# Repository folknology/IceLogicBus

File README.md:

# IceLogicBus
#### IceLogicBus is an Ice40 Hx based MidPlane for robust [Tile](https://github.com/folknology/Tiles) expansion

#### IceLogicBus PCB

#### PCB Top

#### PCB Bottom

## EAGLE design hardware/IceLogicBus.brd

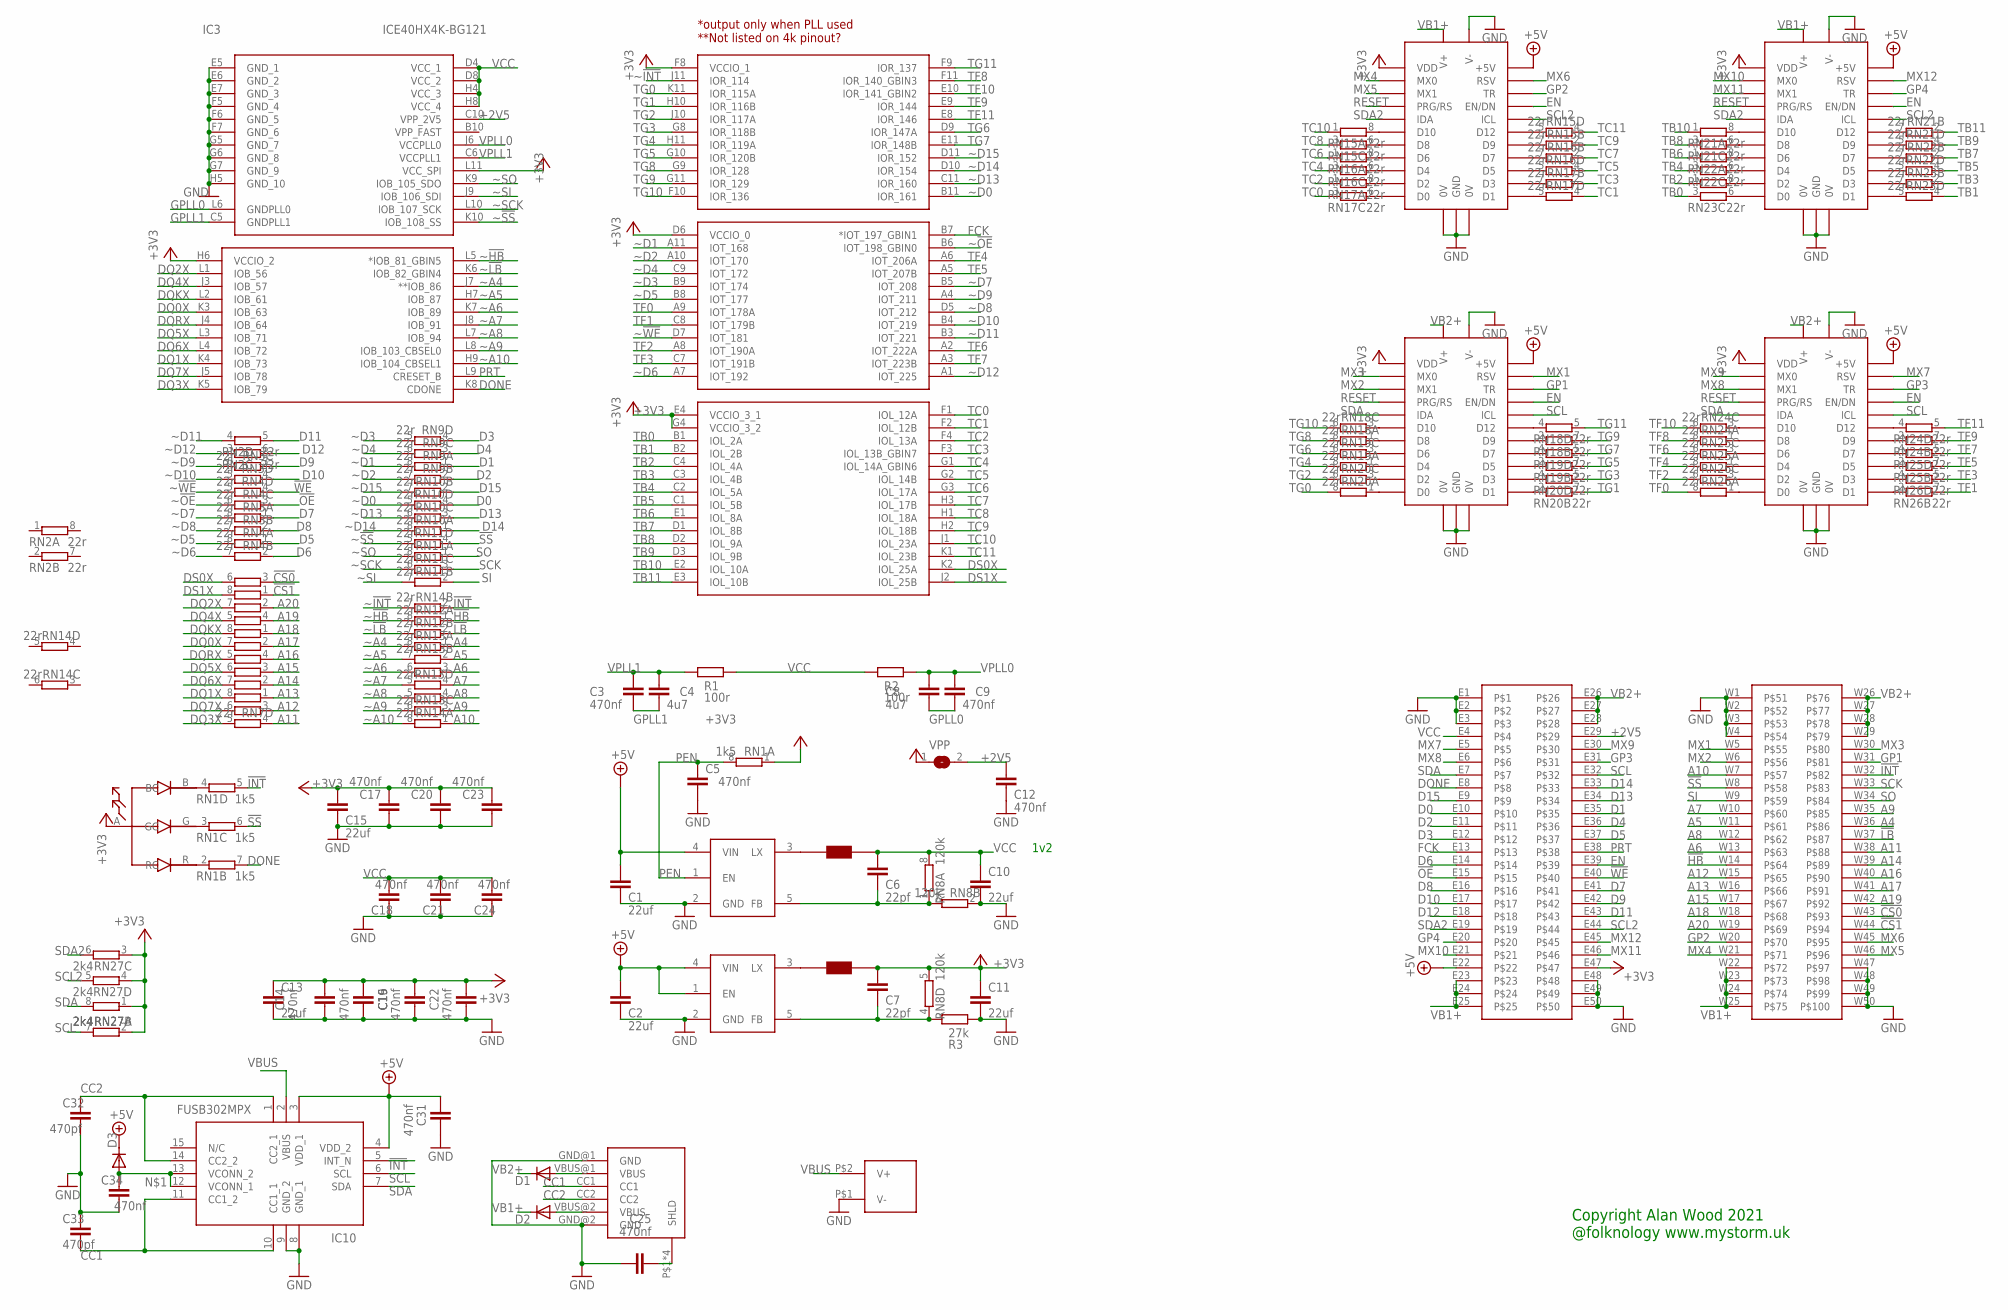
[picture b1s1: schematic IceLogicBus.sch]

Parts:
C1, C2, C10, C11, C13, C15: 22uf; C0603
C3, C5, C9, C12, C14, C16, C17, C18, C19, C20, C21, C22, C23, C24, C25, C31, C34: 470nf; C0402
C4, C8: 4u7; C0402
C6, C7: 22pf; C0402
C32, C33: 470pf; C0402
D1, D2: DIODE-SOD123; SOD123
D3: DIODE-SOD323-W; SOD323-W
IC1, IC2: AP3429/A; TSOP-5/SOT23-5
IC3: ICE40HX4K-BG121; BGA121C80P11X11_900X900X110
IC10: FUSB302MPX; QFN50P250X250X80-15N
L1, L2: NRS4018; NRC4018
L3: RGB_LED; RGB_LED_IMM
R1, R2: 100r; R0402
R3: 27k; R0402
RN1: 1k5; EXB38V
RN2, RN3, RN4, RN5, RN6, RN7, RN9, RN10, RN11, RN12, RN13, RN14, RN15, RN16, RN17, RN18, RN19, RN20, RN21, RN22, RN23, RN24, RN25, RN26: 22r; EXB38V
RN8: 120k; EXB38V
RN27: 2k4; EXB38V
T1, T2, T4, T5: UTILE_LPCARRIER_SMD_MALE_1.27; UTILE_LP
T3: MEZZANINE
U$1: USB-C-6
U$2: XT-XXXT; XT30PW-M
VPP: SJ

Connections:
!CS0: RN5.3 (1), T3.W43
!CS1: RN5.1, T3.W44
!HB: RN12.1, T3.W14
!INT: IC10.5 (INT_N), RN1.5 (2), RN14.2 (1), T3.W32
!LB: RN12.2 (1), T3.W37
!OE: RN4.3 (1), T3.E15
!SS: RN1.6 (2), RN11.4 (1), T3.W8
!WE: RN4.4 (1), T3.E40
+2V5: C12.2, IC3.C10 (VPP_2V5), T3.E29, VPP.2
+3V3: C7.2, C11.1, C13.1, C14.2, C15.2, C16.2, C17.1, C19.2, C20.1, C22.2, C23.1, IC3.D6 (VCCIO_0), IC3.E4 (VCCIO_3_1), IC3.F8 (VCCIO_1), IC3.G4 (VCCIO_3_2), IC3.H6 (VCCIO_2), IC3.L11 (VCC_SPI), L2.P$2, L3.A (ANODE), RN1.1, RN8.5 (2), RN27.1, RN27.2 (1), RN27.3 (1), RN27.4 (1), T1.P$18 (VDD), T2.P$18 (VDD), T3.E47, T4.P$18 (VDD), T5.P$18 (VDD), VPP.1
+5V: C1.2, C2.2, C31.2, D3.C, IC1.4 (VIN), IC2.1 (EN), IC2.4 (VIN), IC10.3 (VDD_1), IC10.4 (VDD_2), T1.P$43 (+5V), T2.P$43 (+5V), T3.E22, T4.P$43 (+5V), T5.P$43 (+5V)
A4: RN13.1, T3.W36
A5: RN13.2 (1), T3.W11
A6: RN12.3 (1), T3.W13
A7: RN13.4 (1), T3.W10
A8: RN12.4 (1), T3.W12
A9: RN13.3 (1), T3.W35
A10: RN14.1, T3.W7
A11: RN7.4 (1), T3.W38
A12: RN7.3 (1), T3.W15
A13: RN7.1, T3.W16
A14: RN7.2 (1), T3.W39
A15: RN6.3 (1), T3.W17
A16: RN6.4 (1), T3.W40
A17: RN6.2 (1), T3.W41
A18: RN6.1, T3.W18
A19: RN5.4 (1), T3.W42
A20: RN5.2 (1), T3.W19
CC1: C33.1, IC10.10 (CC1_1), IC10.11 (CC1_2), U$1.CC1
CC2: C32.2, IC10.1 (CC2_1), IC10.14 (CC2_2), U$1.CC2
D0: RN10.4 (1), T3.E10
D1: RN9.1, T3.E35
D2: RN9.2 (1), T3.E11
D3: RN9.4 (1), T3.E12
D4: RN9.3 (1), T3.E36
D5: RN4.1, T3.E37
D6: RN4.2 (1), T3.E14
D7: RN3.1, T3.E41
D8: RN3.2 (1), T3.E16
D9: RN3.3 (1), T3.E42
D10: RN3.4 (1), T3.E17
D11: RN2.5 (2), T3.E43
D12: RN2.6 (2), T3.E18
D13: RN10.3 (1), T3.E34
D14: RN10.1, T3.E33
D15: RN10.2 (1), T3.E9
DONE: IC3.K8 (CDONE), RN1.7 (2), T3.E8
DQ0X: IC3.K3 (IOB_63), RN6.7 (2)
DQ1X: IC3.K4 (IOB_73), RN7.8 (2)
DQ2X: IC3.L1 (IOB_56), RN5.7 (2)
DQ3X: IC3.K5 (IOB_79), RN7.5 (2)
DQ4X: IC3.J3 (IOB_57), RN5.5 (2)
DQ5X: IC3.L3 (IOB_71), RN6.6 (2)
DQ6X: IC3.L4 (IOB_72), RN7.7 (2)
DQ7X: IC3.J5 (IOB_78), RN7.6 (2)
DQKX: IC3.L2 (IOB_61), RN6.8 (2)
DQRX: IC3.J4 (IOB_64), RN6.5 (2)
DS0X: IC3.K2 (IOL_25A), RN5.6 (2)
DS1X: IC3.J2 (IOL_25B), RN5.8 (2)
EN: T1.P$40 (EN/DN), T2.P$40 (EN/DN), T3.E39, T4.P$40 (EN/DN), T5.P$40 (EN/DN)
FCK: IC3.B7 (*IOT_197_GBIN1), T3.E13
GND: C1.1, C2.1, C5.2, C10.2, C11.2, C12.1, C13.2, C14.1, C15.1, C16.1, C17.2, C18.1, C19.1, C20.2, C21.1, C22.1, C23.2, C24.1, C25.1, C31.1, C32.1, C33.2, C34.1, IC1.2 (GND), IC2.2 (GND), IC3.E5 (GND_1), IC3.E6 (GND_2), IC3.E7 (GND_3), IC3.F5 (GND_4), IC3.F6 (GND_5), IC3.F7 (GND_6), IC3.G5 (GND_7), IC3.G6 (GND_8), IC3.G7 (GND_9), IC3.H5 (GND_10), IC10.8 (GND_1), IC10.9 (GND_2), R3.2, RN8.2 (1), T1.0V@1 (0V), T1.0V@2 (0V), T1.P$1 (V-), T1.P$2 (V-), T1.P$3 (V-), T1.P$4 (V-), T1.P$5 (V-), T1.P$6 (V-), T1.P$7 (GND), T1.P$26 (V-), T1.P$27 (V-), T1.P$28 (V-), T1.P$29 (V-), T1.P$30 (V-), T1.P$31 (V-), T1.P$32 (GND), T2.0V@1 (0V), T2.0V@2 (0V), T2.P$1 (V-), T2.P$2 (V-), T2.P$3 (V-), T2.P$4 (V-), T2.P$5 (V-), T2.P$6 (V-), T2.P$7 (GND), T2.P$26 (V-), T2.P$27 (V-), T2.P$28 (V-), T2.P$29 (V-), T2.P$30 (V-), T2.P$31 (V-), T2.P$32 (GND), T3.E1, T3.E2, T3.E3, T3.E48, T3.E49, T3.E50, T3.W1, T3.W2, T3.W3, T3.W4, T3.W47, T3.W48, T3.W49, T3.W50, T4.0V@1 (0V), T4.0V@2 (0V), T4.P$1 (V-), T4.P$2 (V-), T4.P$3 (V-), T4.P$4 (V-), T4.P$5 (V-), T4.P$6 (V-), T4.P$7 (GND), T4.P$26 (V-), T4.P$27 (V-), T4.P$28 (V-), T4.P$29 (V-), T4.P$30 (V-), T4.P$31 (V-), T4.P$32 (GND), T5.0V@1 (0V), T5.0V@2 (0V), T5.P$1 (V-), T5.P$2 (V-), T5.P$3 (V-), T5.P$4 (V-), T5.P$5 (V-), T5.P$6 (V-), T5.P$7 (GND), T5.P$26 (V-), T5.P$27 (V-), T5.P$28 (V-), T5.P$29 (V-), T5.P$30 (V-), T5.P$31 (V-), T5.P$32 (GND), U$1.GND@1 (GND), U$1.GND@2 (GND), U$2.P$1 (V-)
GP1: T2.P$41 (TR), T3.W31
GP2: T1.P$41 (TR), T3.W20
GP3: T3.E31, T5.P$41 (TR)
GP4: T3.E20, T4.P$41 (TR)
GPLL0: C8.1, C9.1, IC3.L6 (GNDPLL0)
GPLL1: C3.1, C4.1, IC3.C5 (GNDPLL1)
MX1: T2.P$42 (RSV), T3.W5
MX2: T2.P$16 (MX1), T3.W6
MX3: T2.P$17 (MX0), T3.W30
MX4: T1.P$17 (MX0), T3.W21
MX5: T1.P$16 (MX1), T3.W46
MX6: T1.P$42 (RSV), T3.W45
MX7: T3.E5, T5.P$42 (RSV)
MX8: T3.E6, T5.P$16 (MX1)
MX9: T3.E30, T5.P$17 (MX0)
MX10: T3.E21, T4.P$17 (MX0)
MX11: T3.E46, T4.P$16 (MX1)
MX12: T3.E45, T4.P$42 (RSV)
unnamed: C34.2, D3.A, IC10.12 (VCONN_1), IC10.13 (VCONN_2)
unnamed: L3.G (GC), RN1.3 (1)
unnamed: C25.2, U$1.P$1 (SHLD), U$1.P$2 (SHLD), U$1.P$3 (SHLD), U$1.P$4 (SHLD)
unnamed: L3.R (RC), RN1.2 (1)
unnamed: L3.B (BC), RN1.4 (1)
unnamed: RN23.6 (2), T4.P$8 (D0)
unnamed: RN23.5 (2), T4.P$33 (D1)
unnamed: RN23.8 (2), T4.P$9 (D2)
unnamed: RN23.7 (2), T4.P$34 (D3)
unnamed: RN22.6 (2), T4.P$10 (D4)
unnamed: C7.1, IC2.5 (FB), R3.1, RN8.4 (1)
unnamed: IC2.3 (LX), L2.P$1
unnamed: RN22.5 (2), T4.P$35 (D5)
unnamed: RN22.8 (2), T4.P$11 (D6)
unnamed: RN22.7 (2), T4.P$36 (D7)
unnamed: RN21.6 (2), T4.P$12 (D8)
unnamed: RN21.5 (2), T4.P$37 (D9)
unnamed: RN21.8 (2), T4.P$13 (D10)
unnamed: RN21.7 (2), T4.P$38 (D12)
unnamed: RN17.8 (2), T1.P$9 (D2)
unnamed: RN17.6 (2), T1.P$8 (D0)
unnamed: RN17.7 (2), T1.P$34 (D3)
unnamed: RN17.5 (2), T1.P$33 (D1)
unnamed: RN16.8 (2), T1.P$11 (D6)
unnamed: RN16.6 (2), T1.P$10 (D4)
unnamed: RN16.5 (2), T1.P$35 (D5)
unnamed: RN16.7 (2), T1.P$36 (D7)
unnamed: RN15.8 (2), T1.P$13 (D10)
unnamed: RN15.6 (2), T1.P$12 (D8)
unnamed: RN15.7 (2), T1.P$37 (D9)
unnamed: RN15.5 (2), T1.P$38 (D12)
unnamed: RN26.3 (1), T5.P$9 (D2)
unnamed: RN26.1, T5.P$8 (D0)
unnamed: RN26.4 (1), T5.P$34 (D3)
unnamed: RN26.2 (1), T5.P$33 (D1)
unnamed: RN25.3 (1), T5.P$11 (D6)
unnamed: RN25.1, T5.P$10 (D4)
unnamed: RN25.4 (1), T5.P$36 (D7)
unnamed: RN25.2 (1), T5.P$35 (D5)
unnamed: RN24.3 (1), T5.P$13 (D10)
unnamed: RN24.1, T5.P$12 (D8)
unnamed: RN24.4 (1), T5.P$38 (D12)
unnamed: RN24.2 (1), T5.P$37 (D9)
unnamed: RN20.3 (1), T2.P$9 (D2)
unnamed: RN20.1, T2.P$8 (D0)
unnamed: RN20.4 (1), T2.P$34 (D3)
unnamed: RN20.2 (1), T2.P$33 (D1)
unnamed: RN19.3 (1), T2.P$11 (D6)
unnamed: RN19.1, T2.P$10 (D4)
unnamed: RN19.4 (1), T2.P$36 (D7)
unnamed: RN19.2 (1), T2.P$35 (D5)
unnamed: RN18.3 (1), T2.P$13 (D10)
unnamed: RN18.1, T2.P$12 (D8)
unnamed: RN18.4 (1), T2.P$38 (D12)
unnamed: RN18.2 (1), T2.P$37 (D9)
unnamed: C6.1, IC1.5 (FB), RN8.1, RN8.7 (2)
unnamed: IC1.3 (LX), L1.P$1
PEN: C5.1, IC1.1 (EN), RN1.8 (2)
PRT: IC3.L9 (CRESET_B), T3.E38
RESET: T1.P$15 (PRG/RS), T2.P$15 (PRG/RS), T4.P$15 (PRG/RS), T5.P$15 (PRG/RS)
SCK: RN11.3 (1), T3.W33
SCL: IC10.6 (SCL), RN27.7 (2), T2.P$39 (ICL), T3.E32, T5.P$39 (ICL)
SCL2: RN27.5 (2), T1.P$39 (ICL), T3.E44, T4.P$39 (ICL)
SDA: IC10.7 (SDA), RN27.8 (2), T2.P$14 (IDA), T3.E7, T5.P$14 (IDA)
SDA2: RN27.6 (2), T1.P$14 (IDA), T3.E19, T4.P$14 (IDA)
SI: RN11.2 (1), T3.W9
SO: RN11.1, T3.W34
TB0: IC3.B1 (IOL_2A), RN23.3 (1)
TB1: IC3.B2 (IOL_2B), RN23.4 (1)
TB2: IC3.C4 (IOL_4A), RN23.1
TB3: IC3.C3 (IOL_4B), RN23.2 (1)
TB4: IC3.C2 (IOL_5A), RN22.3 (1)
TB5: IC3.C1 (IOL_5B), RN22.4 (1)
TB6: IC3.E1 (IOL_8A), RN22.1
TB7: IC3.D1 (IOL_8B), RN22.2 (1)
TB8: IC3.D2 (IOL_9A), RN21.3 (1)
TB9: IC3.D3 (IOL_9B), RN21.4 (1)
TB10: IC3.E2 (IOL_10A), RN21.1
TB11: IC3.E3 (IOL_10B), RN21.2 (1)
TC0: IC3.F1 (IOL_12A), RN17.3 (1)
TC1: IC3.F2 (IOL_12B), RN17.4 (1)
TC2: IC3.F4 (IOL_13A), RN17.1
TC3: IC3.F3 (IOL_13B_GBIN7), RN17.2 (1)
TC4: IC3.G1 (IOL_14A_GBIN6), RN16.3 (1)
TC5: IC3.G2 (IOL_14B), RN16.4 (1)
TC6: IC3.G3 (IOL_17A), RN16.1
TC7: IC3.H3 (IOL_17B), RN16.2 (1)
TC8: IC3.H1 (IOL_18A), RN15.3 (1)
TC9: IC3.H2 (IOL_18B), RN15.2 (1)
TC10: IC3.J1 (IOL_23A), RN15.1
TC11: IC3.K1 (IOL_23B), RN15.4 (1)
TF0: IC3.A9 (IOT_178A), RN26.8 (2)
TF1: IC3.C8 (IOT_179B), RN26.7 (2)
TF2: IC3.A8 (IOT_190A), RN26.6 (2)
TF3: IC3.C7 (IOT_191B), RN26.5 (2)
TF4: IC3.A6 (IOT_206A), RN25.8 (2)
TF5: IC3.A5 (IOT_207B), RN25.7 (2)
TF6: IC3.A2 (IOT_222A), RN25.6 (2)
TF7: IC3.A3 (IOT_223B), RN25.5 (2)
TF8: IC3.F11 (IOR_140_GBIN3), RN24.8 (2)
TF9: IC3.E9 (IOR_144), RN24.7 (2)
TF10: IC3.E10 (IOR_141_GBIN2), RN24.6 (2)
TF11: IC3.E8 (IOR_146), RN24.5 (2)
TG0: IC3.K11 (IOR_115A), RN20.8 (2)
TG1: IC3.H10 (IOR_116B), RN20.7 (2)
TG2: IC3.J10 (IOR_117A), RN20.6 (2)
TG3: IC3.G8 (IOR_118B), RN20.5 (2)
TG4: IC3.H11 (IOR_119A), RN19.8 (2)
TG5: IC3.G10 (IOR_120B), RN19.7 (2)
TG6: IC3.D9 (IOR_147A), RN19.6 (2)
TG7: IC3.E11 (IOR_148B), RN19.5 (2)
TG8: IC3.G9 (IOR_128), RN18.8 (2)
TG9: IC3.G11 (IOR_129), RN18.7 (2)
TG10: IC3.F10 (IOR_136), RN18.6 (2)
TG11: IC3.F9 (IOR_137), RN18.5 (2)
VB1+: D2.C, T1.P$20 (V+), T1.P$21 (V+), T1.P$22 (V+), T1.P$23 (V+), T1.P$24 (V+), T1.P$25 (V+), T1.P$45 (V+), T1.P$46 (V+), T1.P$47 (V+), T1.P$48 (V+), T1.P$49 (V+), T1.P$50 (V+), T3.E23, T3.E24, T3.E25, T3.W22, T3.W23, T3.W24, T3.W25, T4.P$20 (V+), T4.P$21 (V+), T4.P$22 (V+), T4.P$23 (V+), T4.P$24 (V+), T4.P$25 (V+), T4.P$45 (V+), T4.P$46 (V+), T4.P$47 (V+), T4.P$48 (V+), T4.P$49 (V+), T4.P$50 (V+)
VB2+: D1.C, T2.P$20 (V+), T2.P$21 (V+), T2.P$22 (V+), T2.P$23 (V+), T2.P$24 (V+), T2.P$25 (V+), T2.P$45 (V+), T2.P$46 (V+), T2.P$47 (V+), T2.P$48 (V+), T2.P$49 (V+), T2.P$50 (V+), T3.E26, T3.E27, T3.E28, T3.W26, T3.W27, T3.W28, T3.W29, T5.P$20 (V+), T5.P$21 (V+), T5.P$22 (V+), T5.P$23 (V+), T5.P$24 (V+), T5.P$25 (V+), T5.P$45 (V+), T5.P$46 (V+), T5.P$47 (V+), T5.P$48 (V+), T5.P$49 (V+), T5.P$50 (V+)
VBUS: D1.A, D2.A, IC10.2 (VBUS), U$1.VBUS@1 (VBUS), U$1.VBUS@2 (VBUS), U$2.P$2 (V+)
VCC: C6.2, C10.1, C18.2, C21.2, C24.2, IC3.D4 (VCC_1), IC3.D8 (VCC_2), IC3.H4 (VCC_3), IC3.H8 (VCC_4), L1.P$2, R1.1, R2.2, RN8.8 (2), T3.E4
VPLL0: C8.2, C9.2, IC3.J6 (VCCPLL0), R2.1
VPLL1: C3.2, C4.2, IC3.C6 (VCCPLL1), R1.2
~!HB: IC3.L5 (*IOB_81_GBIN5), RN12.8 (2)
~!INT: IC3.J11 (IOR_114), RN14.7 (2)
~!LB: IC3.K6 (IOB_82_GBIN4), RN12.7 (2)
~!OE: IC3.B6 (IOT_198_GBIN0), RN4.6 (2)
~!SS: IC3.K10 (IOB_108_SS), RN11.5 (2)
~!WE: IC3.D7 (IOT_181), RN4.5 (2)
~A4: IC3.J7 (**IOB_86), RN13.8 (2)
~A5: IC3.H7 (IOB_87), RN13.7 (2)
~A6: IC3.K7 (IOB_89), RN12.6 (2)
~A7: IC3.J8 (IOB_91), RN13.5 (2)
~A8: IC3.L7 (IOB_94), RN12.5 (2)
~A9: IC3.L8 (IOB_103_CBSEL0), RN13.6 (2)
~A10: IC3.H9 (IOB_104_CBSEL1), RN14.8 (2)
~D0: IC3.B11 (IOR_161), RN10.5 (2)
~D1: IC3.A11 (IOT_168), RN9.8 (2)
~D2: IC3.A10 (IOT_170), RN9.7 (2)
~D3: IC3.B9 (IOT_174), RN9.5 (2)
~D4: IC3.C9 (IOT_172), RN9.6 (2)
~D5: IC3.B8 (IOT_177), RN4.8 (2)
~D6: IC3.A7 (IOT_192), RN4.7 (2)
~D7: IC3.B5 (IOT_208), RN3.8 (2)
~D8: IC3.D5 (IOT_212), RN3.7 (2)
~D9: IC3.A4 (IOT_211), RN3.6 (2)
~D10: IC3.B4 (IOT_219), RN3.5 (2)
~D11: IC3.B3 (IOT_221), RN2.4 (1)
~D12: IC3.A1 (IOT_225), RN2.3 (1)
~D13: IC3.C11 (IOR_160), RN10.6 (2)
~D14: IC3.D10 (IOR_154), RN10.8 (2)
~D15: IC3.D11 (IOR_152), RN10.7 (2)
~SCK: IC3.L10 (IOB_107_SCK), RN11.6 (2)
~SI: IC3.J9 (IOB_106_SDI), RN11.7 (2)
~SO: IC3.K9 (IOB_105_SDO), RN11.8 (2)

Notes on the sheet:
Copyright Alan Wood 2021 @folknology www.mystorm.uk
1v2

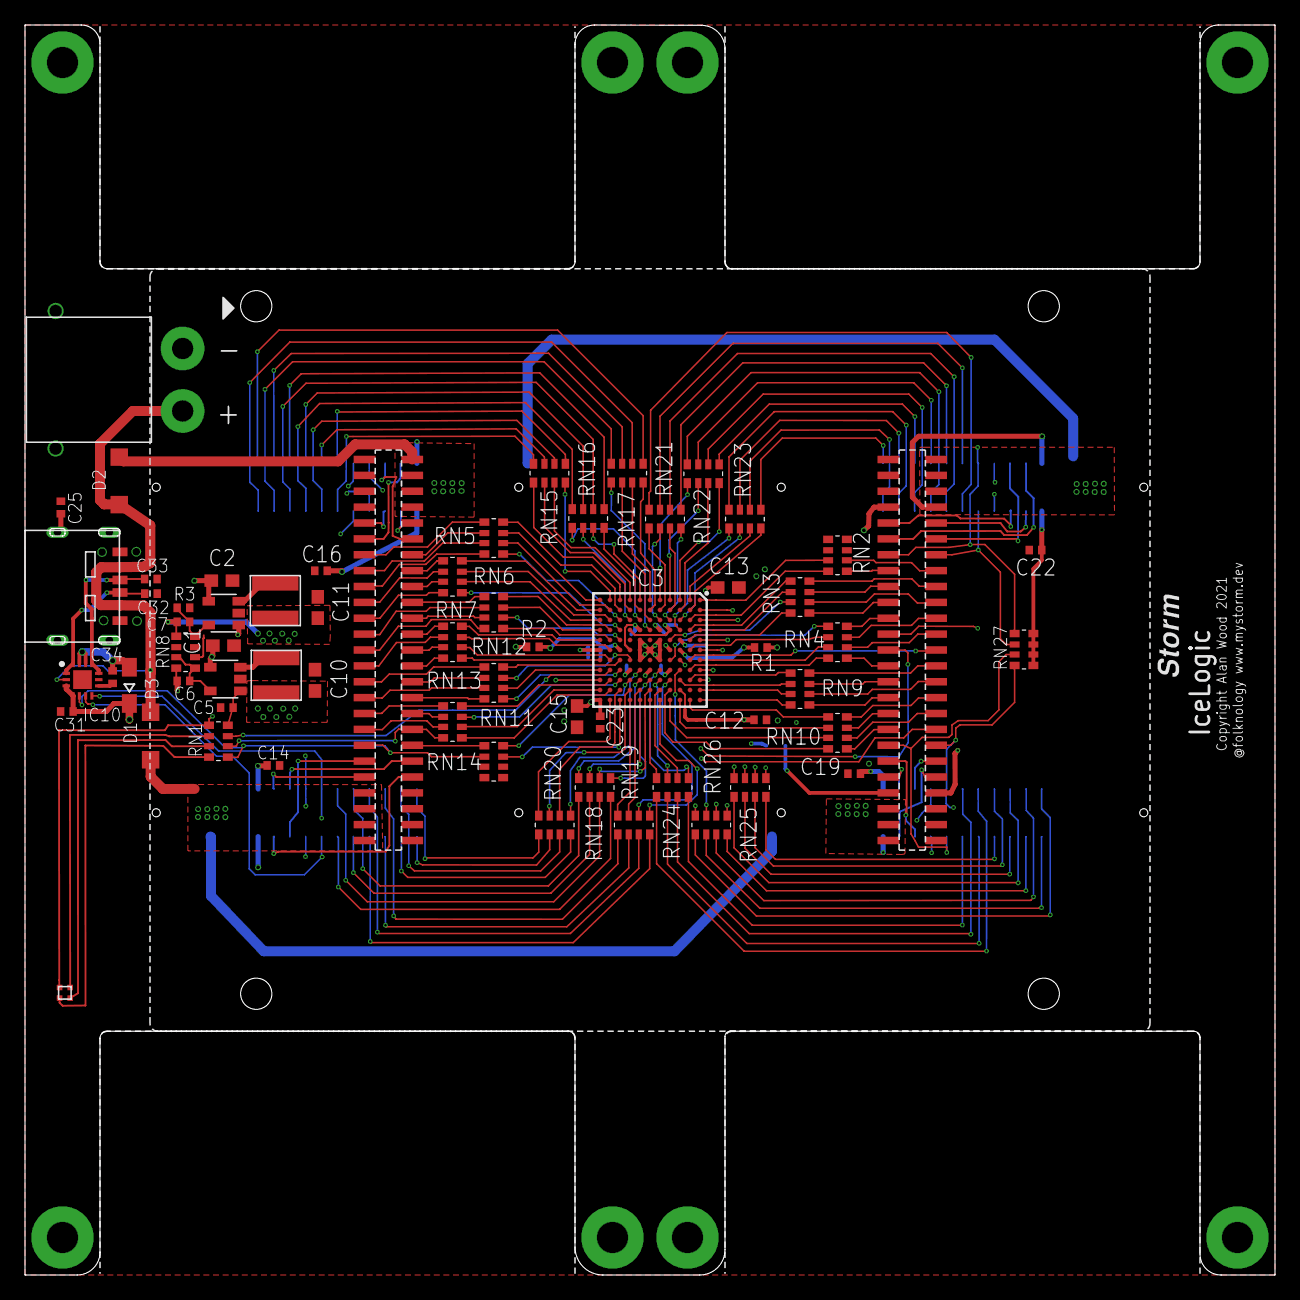
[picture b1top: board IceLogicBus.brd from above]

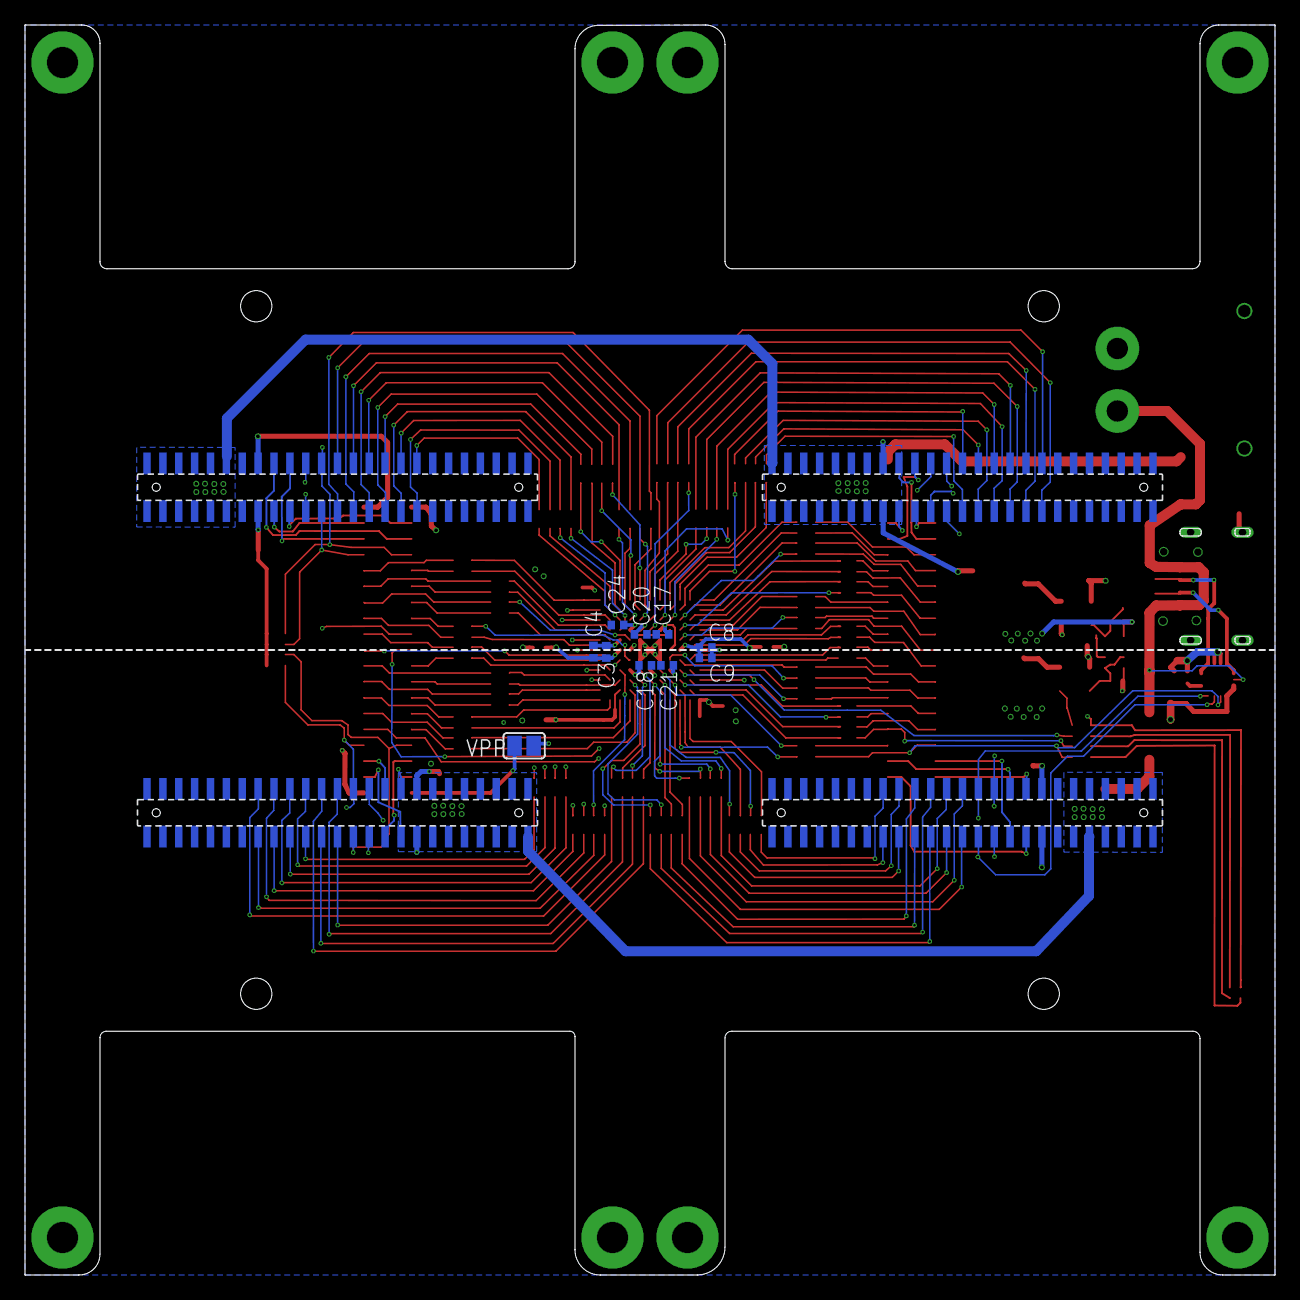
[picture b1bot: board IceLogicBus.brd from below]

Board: 4 copper layers, 100.0 x 100.0 mm, 77 parts (14 on the bottom side), 233 nets.

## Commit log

2022-05-15 Edited Description and added some images and PCB shots and CAD files
2022-05-15 Edited Description and added schematic image for now
2022-05-15 Added link to Tiles repository

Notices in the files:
parts and their libraries:
SparkFun-Aesthetics: Licensing: Creative Commons ShareAlike 4.0 International - https://creativecommons.org/licenses/by-sa/4.0
